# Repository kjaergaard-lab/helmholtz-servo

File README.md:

# Helmholtz Servo

The design contained here is an analogue PID controller, with some
peculiarities specific for controlling the current though the
Helmholtz coil of our apparatus.

## Status
This project is not yet in production use.

## Where to look

This repository contains the KiCad project for the controller. PDF
copies of the schematic, PCB, and documentation can be found in the
*Generated* folder.

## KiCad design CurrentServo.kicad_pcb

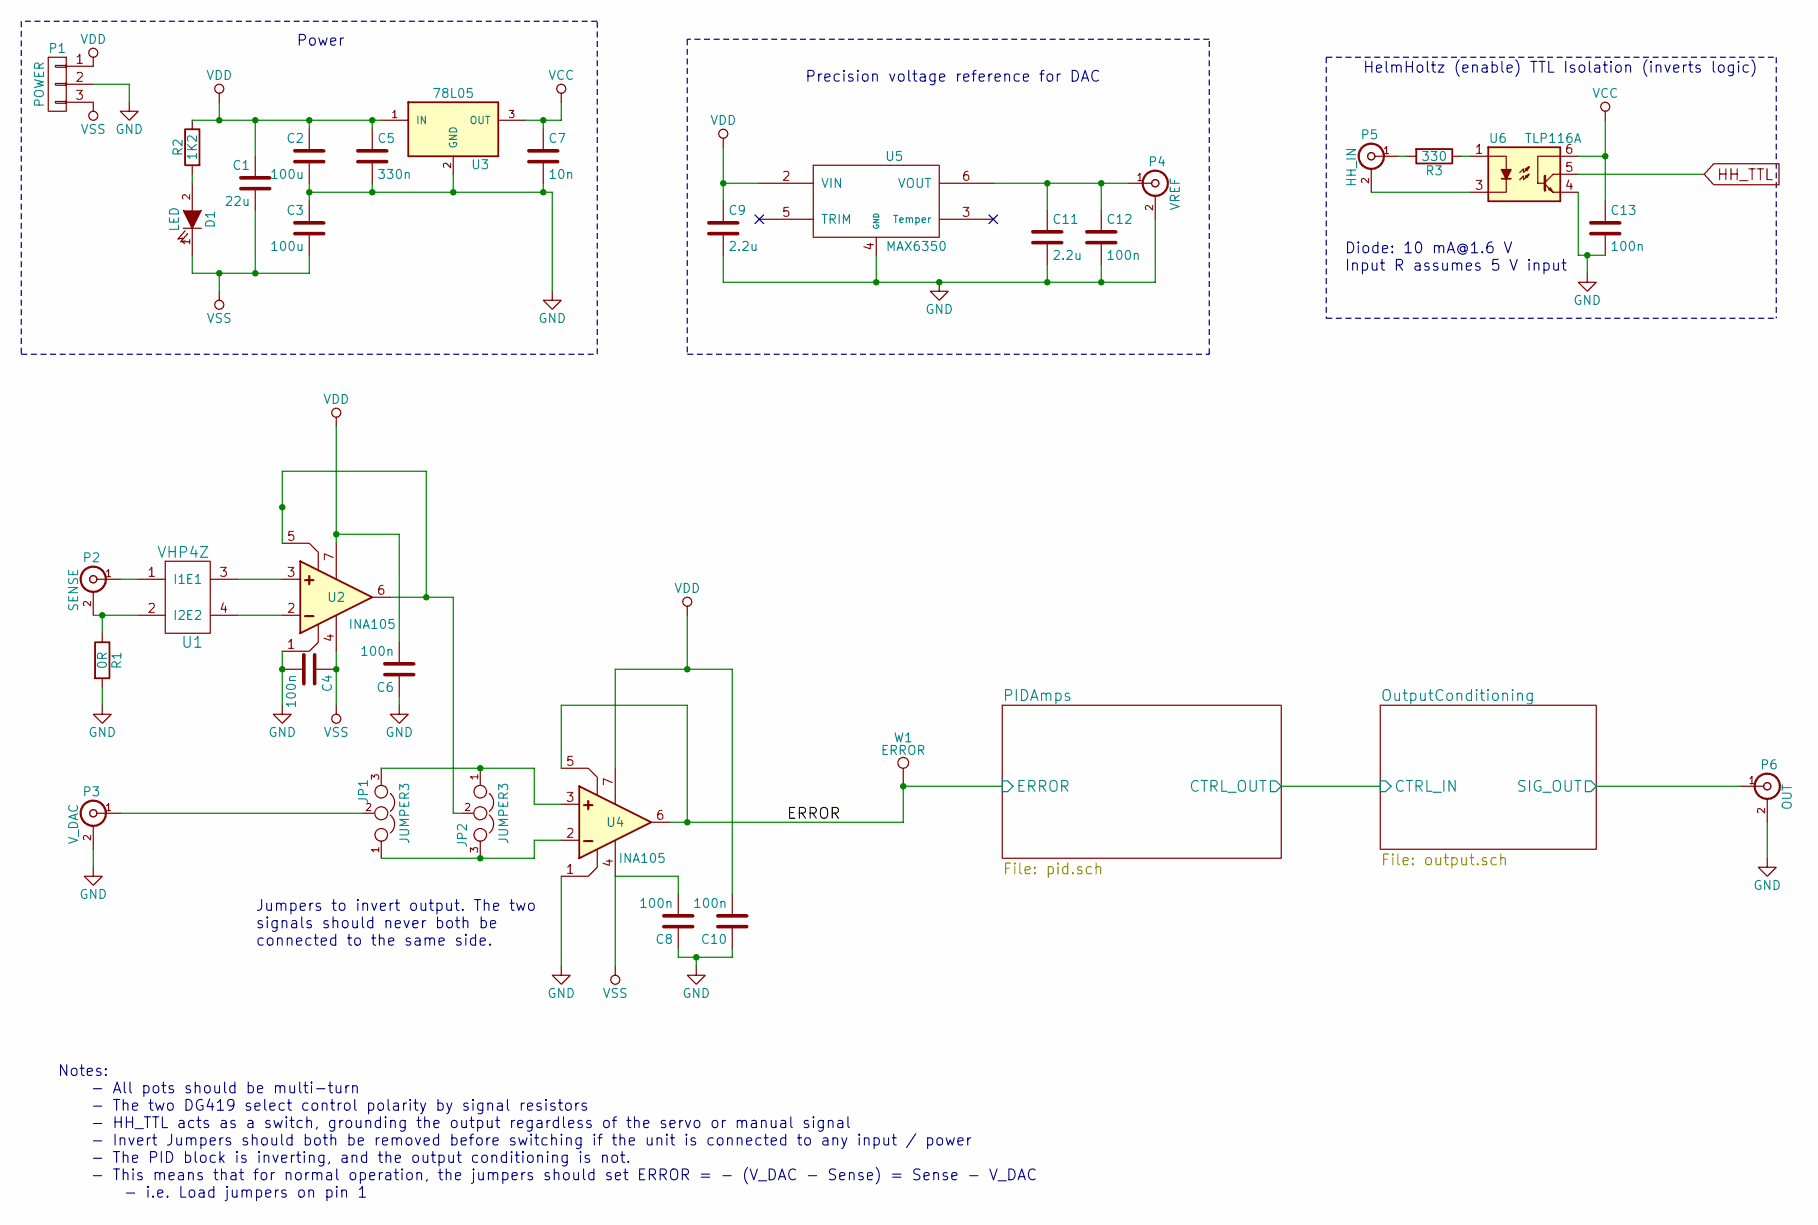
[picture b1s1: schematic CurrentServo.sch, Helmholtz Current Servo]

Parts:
C1: 22u; C_Radial_D10_L13_P5
C2, C3: 100u; C_Radial_D10_L16_P5
C4, C6, C8, C10, C12, C13: 100n; C_0805
C5: 330n; C_0805
C7: 10n; C_0805
C9, C11: 2.2u; C_0805
D1: LED; LED-3MM
JP1, JP2: JUMPER3; Pin_Header_Straight_1x03
P1: POWER; TerminalBlock_Pheonix_PT-3.5mm_3pol
P2: SENSE; BNC_Socket_TYCO-AMP_LargePads
P3: V_DAC; BNC_Socket_TYCO-AMP_LargePads
P4: VREF; BNC_Socket_TYCO-AMP_LargePads
P5: HH_IN; BNC_Socket_TYCO-AMP_LargePads
P6: OUT; BNC_Socket_TYCO-AMP_LargePads
R1: 0R; R_0805
R2: 1K2; R_1206
R3: 330; R_1206
U1: VHP4Z
U2, U4: INA105; DIP-8_W7.62mm
U3: 78L05; TO-220_Neutral123_Vertical
U5: MAX6350; DIP-8_W7.62mm
U6: TLP116A
W1: ERROR; PINTST

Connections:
/OutputConditioning/SIG_OUT: P6.1 (In); also elsewhere on the board
/PIDAmps/ERROR: U4.5 (BALANCE), U4.6 (OUTPUT), W1.1; also elsewhere on the board
GND: C2.2, C3.1, C4.2, C5.2, C6.1, C7.2, C8.1, C9.2, C10.1, C11.2, C12.2, C13.2, P1.2, P3.2 (Ext), P4.2 (Ext), P6.2 (Ext), R1.2, U2.1 (BAL/COMP), U3.2 (GND), U4.1 (BAL/COMP), U5.4 (GND), U6.4; also elsewhere on the board
HH_TTL: U6.5; also elsewhere on the board
unnamed: C11.1, C12.1, P4.1 (In), U5.6 (VOUT)
unnamed: D1.2 (A), R2.2
unnamed: JP1.1, JP2.3, U4.2 (INVERTING)
unnamed: JP1.2, P3.1 (In)
unnamed: JP1.3, JP2.1, U4.3 (NON)
unnamed: JP2.2, U2.5 (BALANCE), U2.6 (OUTPUT)
unnamed: P2.1 (In), U1.1 (I1)
unnamed: P2.2 (Ext), R1.1, U1.2 (I2)
unnamed: P5.1 (In), R3.2
unnamed: P5.2 (Ext), U6.3
unnamed: R3.1, U6.1
unnamed: U1.3 (E1), U2.3 (NON)
unnamed: U1.4 (E2), U2.2 (INVERTING)
VCC: C7.1, C13.1, U3.3 (OUT), U6.6; also elsewhere on the board
VDD: C1.1, C2.1, C5.1, C6.2, C9.1, C10.2, P1.1, R2.1, U2.7 (V+), U3.1 (IN), U4.7 (V+), U5.2 (VIN); also elsewhere on the board
VSS: C1.2, C3.2, C4.1, C8.2, D1.1 (K), P1.3, U2.4 (V-), U4.4 (V-); also elsewhere on the board

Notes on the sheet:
Power
HelmHoltz (enable) TTL Isolation (inverts logic)
Precision voltage reference for DAC
Diode: 10 mA@1.6 V Input R assumes 5 V input
Notes: - All pots should be multi-turn - The two DG419 select control polarity by signal resistors - HH_TTL acts as a switch, grounding the output regardless of the servo or manual signal - Invert Jumpers should both be removed before switching if the unit is connected to any input / power - The PI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
Jumpers to invert output. The two signals should never both be connected to the same side.

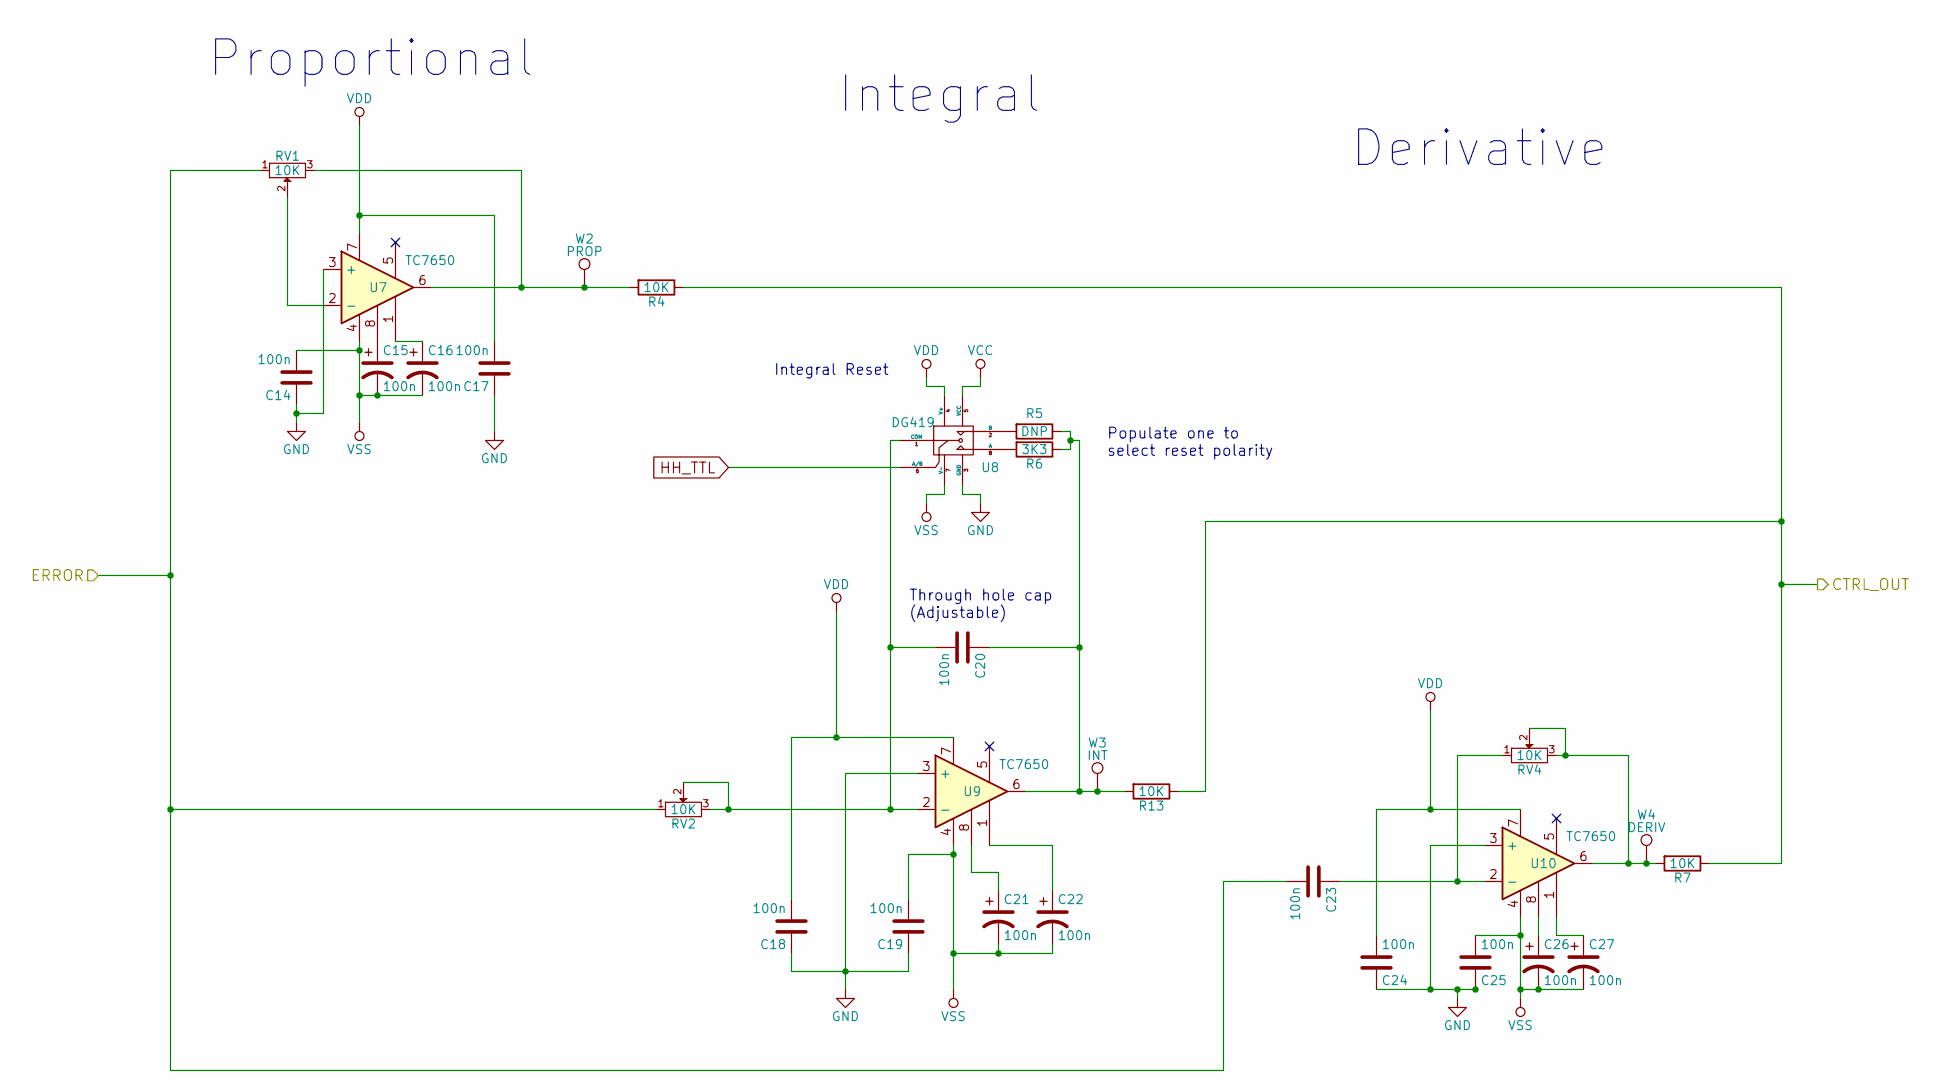
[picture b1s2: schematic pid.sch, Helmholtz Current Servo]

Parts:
C14, C15, C16, C17, C18, C19, C21, C22, C23, C24, C25, C26, C27: 100n; C_0805
C20: 100n; Resistor_SMD+THTuniversal_0805to1206_RM10_HandSoldering
R4, R7, R13: 10K; R_1206
R5: DNP; R_1206
R6: 3K3; R_1206
RV1, RV2, RV4: 10K; Potentiometer_Bourns_3296W_3-8Zoll_Inline_ScrewUp
U7, U9, U10: TC7650; DIP-8_W7.62mm
U8: DG419; SOIC-8-N
W2: PROP; PINTST
W3: INT; PINTST
W4: DERIV; PINTST

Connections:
/OutputConditioning/CTRL_IN: R4.1, R7.1, R13.1; also elsewhere on the board
/PIDAmps/ERROR: C23.2, RV1.1, RV2.1; also elsewhere on the board
GND: C14.1, C17.1, C18.1, C19.1, C24.1, C25.1, U7.3 (+), U8.3 (GND), U9.3 (+), U10.3 (+); also elsewhere on the board
HH_TTL: U8.6 (A/B); also elsewhere on the board
unnamed: C15.1, U7.8
unnamed: C16.1, U7.1
unnamed: C20.1, R5.1, R6.1, R13.2, U9.6, W3.1
unnamed: C20.2, RV2.2, RV2.3, U8.1 (COM), U9.2 (-)
unnamed: C21.1, U9.8
unnamed: C22.1, U9.1
unnamed: C23.1, RV4.1, U10.2 (-)
unnamed: C26.1, U10.8
unnamed: C27.1, U10.1
unnamed: R4.2, RV1.3, U7.6, W2.1
unnamed: R5.2, U8.2 (B)
unnamed: R6.2, U8.8 (A)
unnamed: R7.2, RV4.2, RV4.3, U10.6, W4.1
unnamed: RV1.2, U7.2 (-)
VCC: U8.5 (VCC); also elsewhere on the board
VDD: C17.2, C18.2, C24.2, U7.7, U8.4 (V+), U9.7, U10.7; also elsewhere on the board
VSS: C14.2, C15.2, C16.2, C19.2, C21.2, C22.2, C25.2, C26.2, C27.2, U7.4, U8.7 (V-), U9.4, U10.4; also elsewhere on the board

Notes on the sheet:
Through hole cap (Adjustable)
Proportional
Derivative
Integral
Populate one to select reset polarity
Integral Reset

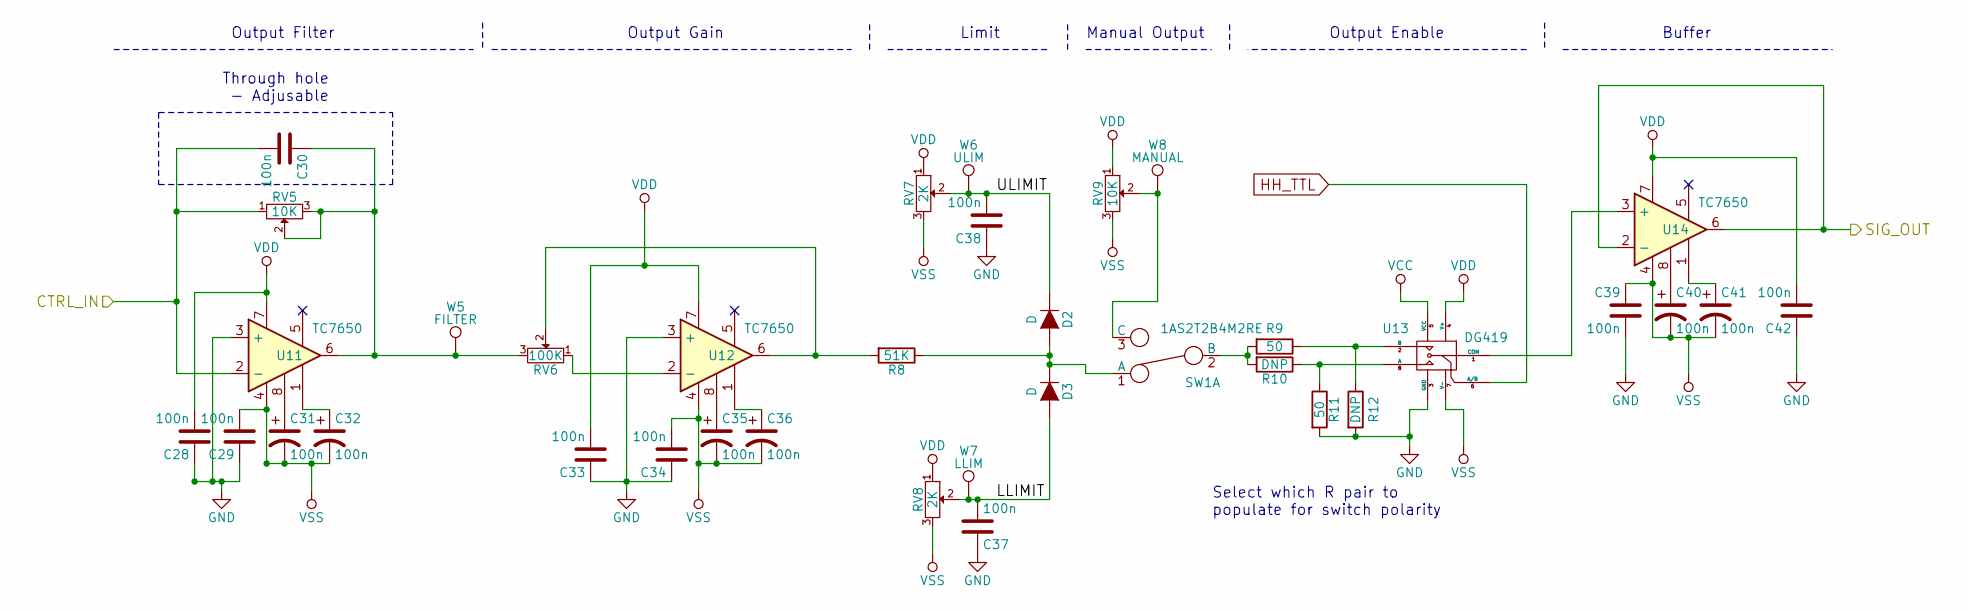
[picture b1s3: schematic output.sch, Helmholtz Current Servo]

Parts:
C28, C29, C31, C32, C33, C34, C35, C36, C37, C38, C39, C40, C41, C42: 100n; C_0805
C30: 100n; Resistor_SMD+THTuniversal_0805to1206_RM10_HandSoldering
D2, D3: D; Diode_DO-35_SOD27_Horizontal_RM10
R8: 51K; R_1206
R9, R11: 50; R_1206
R10, R12: DNP; R_1206
RV5, RV9: 10K; Potentiometer_Bourns_3296W_3-8Zoll_Inline_ScrewUp
RV6: 100K; Potentiometer_Bourns_3296W_3-8Zoll_Inline_ScrewUp
RV7, RV8: 2K; Potentiometer_Bourns_3296W_3-8Zoll_Inline_ScrewUp
SW1: 1AS2T2B4M2RE; Switch_SPDT_4.7mm
U11, U12, U14: TC7650; DIP-8_W7.62mm
U13: DG419; SOIC-8-N
W5: FILTER; PINTST
W6: ULIM; PINTST
W7: LLIM; PINTST
W8: MANUAL; PINTST

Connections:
/OutputConditioning/CTRL_IN: C30.2, RV5.1, U11.2 (-); also elsewhere on the board
/OutputConditioning/LLIMIT: C37.2, D3.2 (A), RV8.2, W7.1
/OutputConditioning/SIG_OUT: U14.2 (-), U14.6; also elsewhere on the board
/OutputConditioning/ULIMIT: C38.2, D2.1 (K), RV7.2, W6.1
GND: C28.1, C29.1, C33.1, C34.1, C37.1, C38.1, C39.2, C42.1, R11.2, R12.2, U11.3 (+), U12.3 (+), U13.3 (GND); also elsewhere on the board
HH_TTL: U13.6 (A/B); also elsewhere on the board
unnamed: C30.1, RV5.2, RV5.3, RV6.3, U11.6, W5.1
unnamed: C31.1, U11.8
unnamed: C32.1, U11.1
unnamed: C35.1, U12.8
unnamed: C36.1, U12.1
unnamed: C40.1, U14.8
unnamed: C41.1, U14.1
unnamed: D2.2 (A), D3.1 (K), R8.1, SW1.1 (A)
unnamed: R8.2, RV6.2, U12.6
unnamed: R10.1, R11.1, U13.8 (A)
unnamed: R9.2, R10.2, SW1.2 (B)
unnamed: R9.1, R12.1, U13.2 (B)
unnamed: RV6.1, U12.2 (-)
unnamed: RV9.2, SW1.3 (C), W8.1
unnamed: U13.1 (COM), U14.3 (+)
VCC: U13.5 (VCC); also elsewhere on the board
VDD: C28.2, C33.2, C42.2, RV7.1, RV8.1, RV9.1, U11.7, U12.7, U13.4 (V+), U14.7; also elsewhere on the board
VSS: C29.2, C31.2, C32.2, C34.2, C35.2, C36.2, C39.1, C40.2, C41.2, RV7.3, RV8.3, RV9.3, U11.4, U12.4, U13.7 (V-), U14.4; also elsewhere on the board

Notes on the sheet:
Through hole - Adjusable
Limit
Output Enable
Buffer
Output Gain
Output Filter
Select which R pair to populate for switch polarity
Manual Output

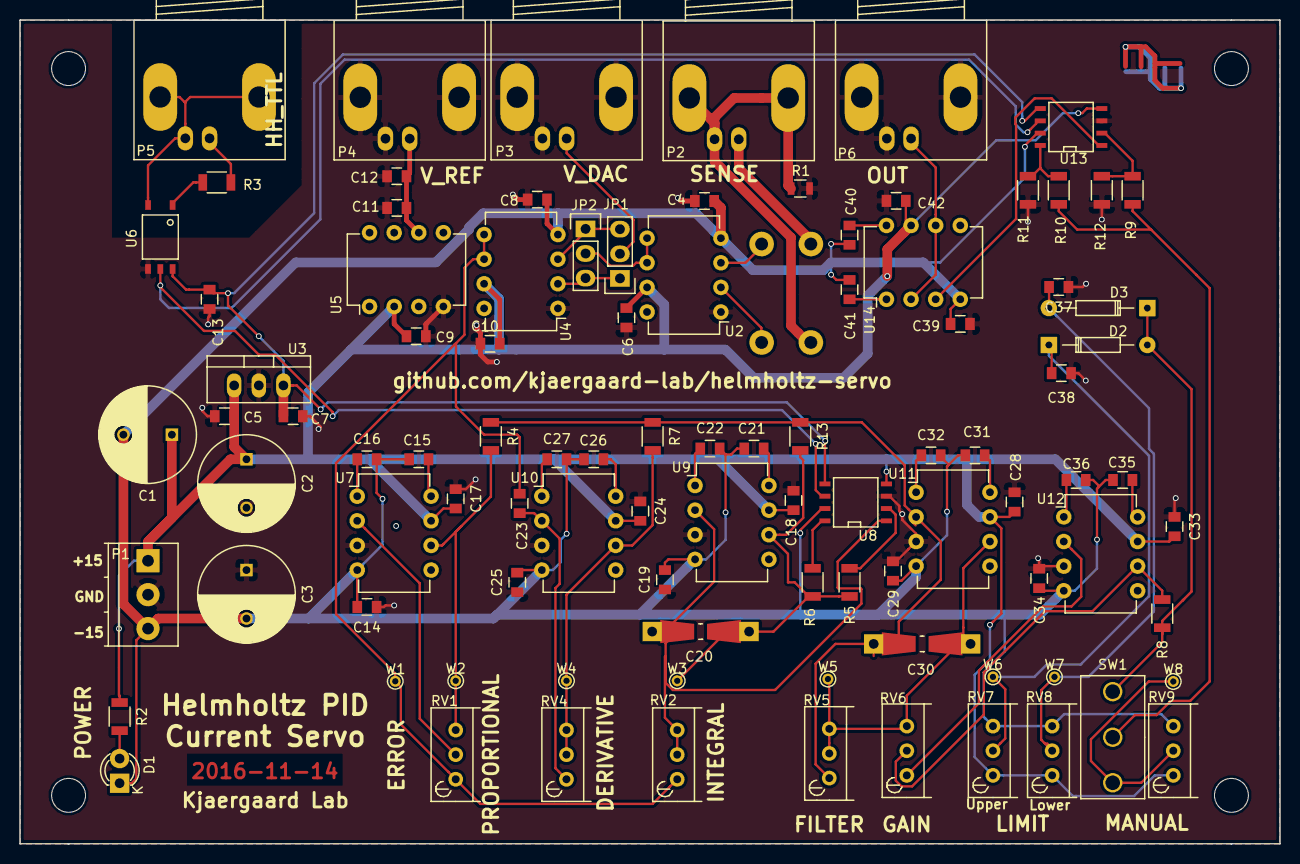
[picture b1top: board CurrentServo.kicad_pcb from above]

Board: 2 copper layers, 130.0 x 85.0 mm, 97 parts (1 on the bottom side), 52 nets.

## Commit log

2016-11-10 First revision design
2016-11-11 Added README
2016-11-14 Files sent for manufacture
2016-12-14 Documented and fixed output gain bug
